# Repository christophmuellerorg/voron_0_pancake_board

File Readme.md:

# Pancake Board

The pancake board is a passive tool board mounting on the back of the MiniAB pancake 
stepper of the Voron 0.1. The board solidly mounts with 20mm brass standoffs to the 
back of the mini after burner mounting screws and provides JST PH connectors 
(2mm pitch) for the two part cooling fans, the hotend fan, a thermistor, 
two switches (for example the X endstop + a klicky probe) as well as the stepper. 
The heater output is provided as a 2x1 Molex Microfit connector and all terminals 
are terminated onto a 2x7 Microfit.

# BOM

For the PCB:
- 1x Molex 43045-1400 (Microfit 2x7) 
- 1x Molex 43045-0200 (Microfit 2x1)
- 4x JST PH 2 Pin, B2B-PH-K-S(LF)(SN)
- 3x JST PH 3 Pin, B3B-PH-K-S(LF)(SN)
- 1x JST PH 4 Pin, B4B-PH-K-S(LF)(SN)

And the appropriate connectors for your cable loom...

# Where can I get it?

- [deepfriedhero](https://deepfriedhero.in/products/voron-v0-1-pancake-stepper-board)
- [pcbway](https://www.pcbway.com/project/shareproject/Pancake_Board.html) Disclaimer: I get 10% commission as store credits which I use for future prototypes.
- Or use the gerber files to order from your favourite PCB manufacturer...

# What is the pinout?

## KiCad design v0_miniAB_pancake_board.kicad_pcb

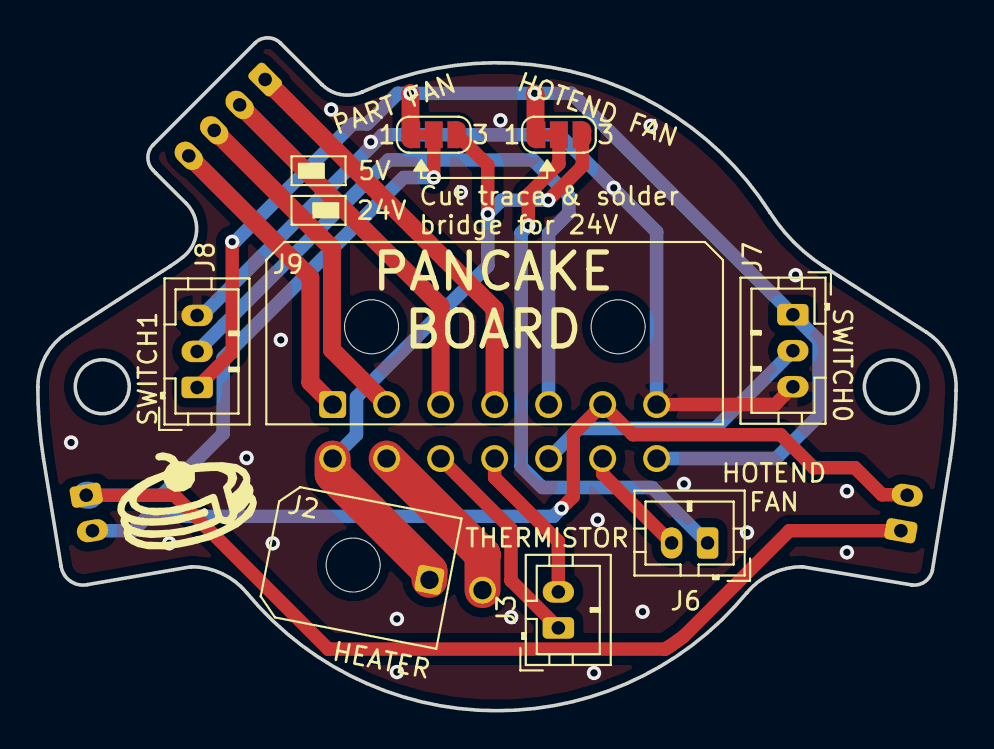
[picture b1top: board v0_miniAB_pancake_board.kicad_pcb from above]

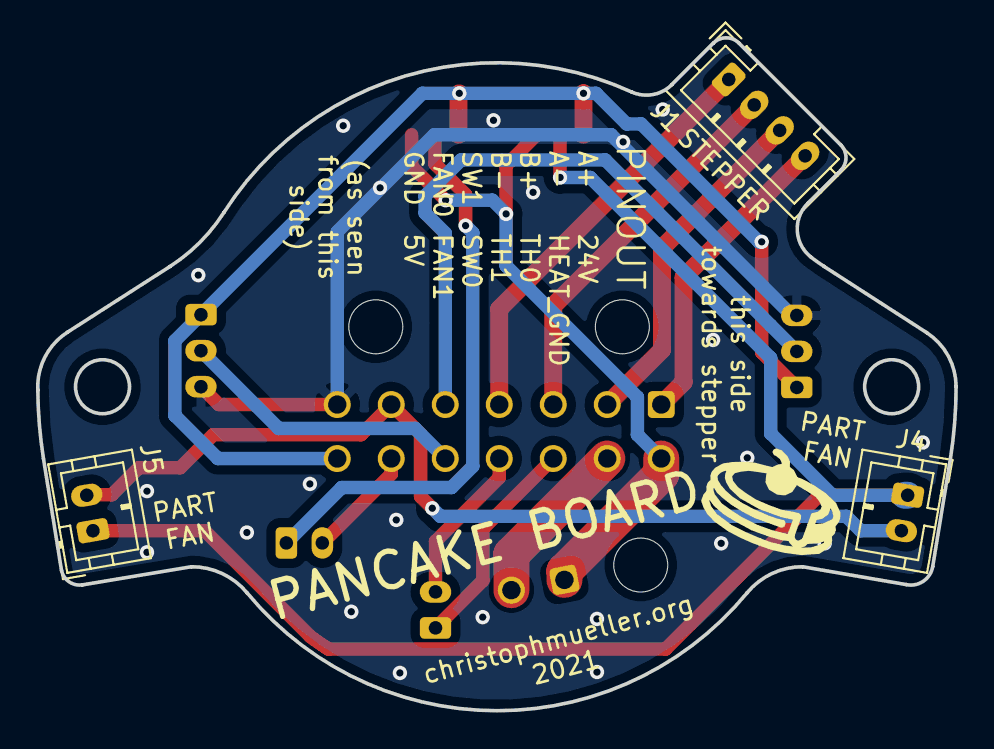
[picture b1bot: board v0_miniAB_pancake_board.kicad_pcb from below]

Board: 2 copper layers, 51.0 x 37.4 mm, 11 parts (3 on the bottom side), 16 nets.

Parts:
J1: Conn_01x04_Female; JST_PH_B4B-PH-K_1x04_P2.00mm_Vertical
J2: Conn_01x02_Female; Molex_Micro-Fit_3.0_43045-0200_2x01_P3.00mm_Horizontal
J3, J4, J5, J6: Conn_01x02_Female; JST_PH_B2B-PH-K_1x02_P2.00mm_Vertical
J7, J8: Conn_01x03_Female; JST_PH_B3B-PH-K_1x03_P2.00mm_Vertical
J9: Conn_02x07_Counter_Clockwise; Molex_Micro-Fit_3.0_43045-1400_2x07_P3.00mm_Horizontal
J10, J11: Conn_01x03_Female; SolderJumper-3_P1.3mm_Bridged12_RoundedPad1.0x1.5mm_NumberL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

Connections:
+5V: J7.1, J8.1, J9.14, J10.1, J11.1
+24V: J2.1, J9.8, J10.3, J11.3
/A+: J1.4, J9.1
/A-: J1.3, J9.2
/B+: J1.2, J9.3
/B-: J1.1, J9.4
/VFAN0: J4.1, J5.1, J10.2
/VFAN1: J6.1, J11.2
/fan0: J4.2, J5.2, J9.6
/fan1: J6.2, J9.13
/heat_gnd: J2.2, J9.9
/sw0: J7.2, J9.12
/sw1: J8.2, J9.5
/therm0: J3.1, J9.10
/therm1: J3.2, J9.11
GND: J7.3, J8.3, J9.7

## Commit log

2021-09-12 beta version \o/
2021-09-12 step file added
2021-09-13 a little bit more clearance around the mounting holes
2021-11-15 STLs added
2021-11-18 some documentation
2021-11-29 connector naming fixed
2022-02-16 Create LICENSE
